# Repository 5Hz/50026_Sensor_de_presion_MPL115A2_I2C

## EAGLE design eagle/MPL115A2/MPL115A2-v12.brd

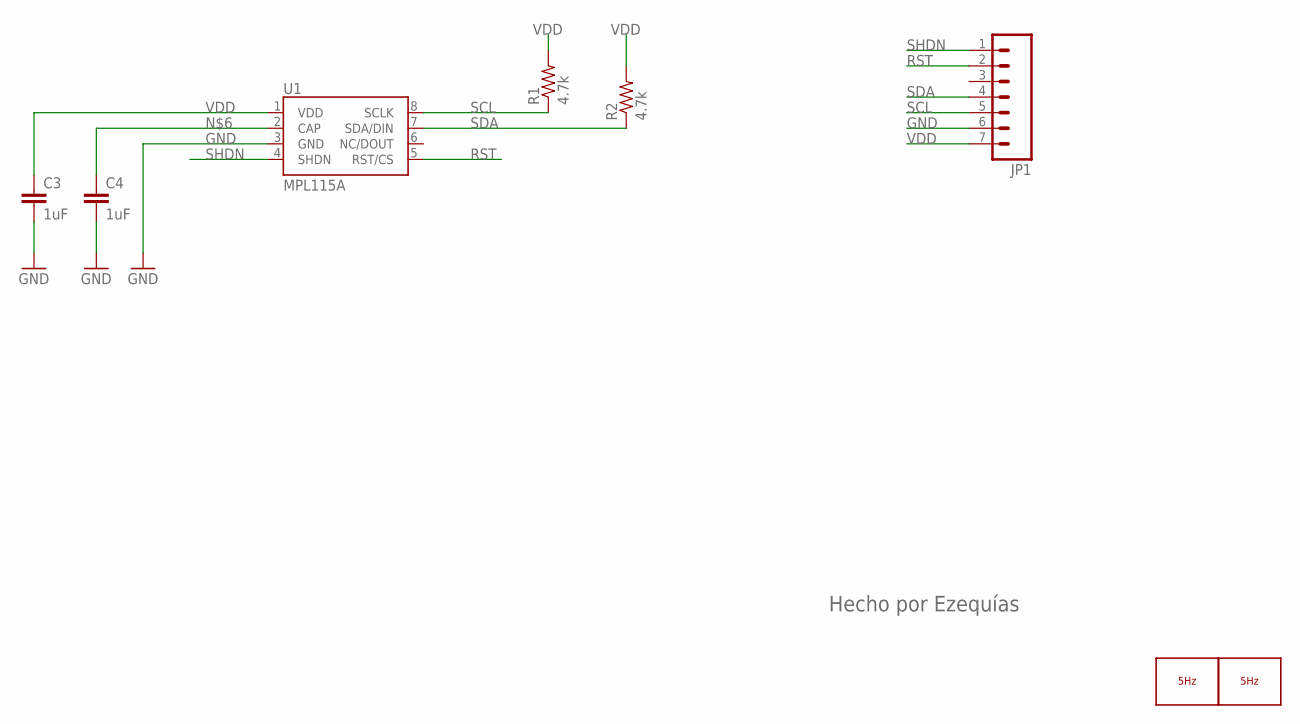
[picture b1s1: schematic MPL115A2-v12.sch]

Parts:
C3, C4: 1uF; 0805-CAP
JP1: M07; 1X07
LOGO1: LOGO_5HZ_H_5MM; 5HZ_LOGO_H_5MM
LOGO2: LOGO_5HZ_MINUSCULAS; 5HZ_LOGO_H_5MM
R1, R2: 4.7k; 1/6W-RES
U1: MPL115A; LGA8

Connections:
GND: C3.2, C4.2, JP1.6, U1.3 (GND)
unnamed: C4.1, U1.2 (CAP)
RST: JP1.2, U1.5 (RST/CS)
SCL: JP1.5, R1.1, U1.8 (SCLK)
SDA: JP1.4, R2.1, U1.7 (SDA/DIN)
SHDN: JP1.1, U1.4 (SHDN)
VDD: C3.1, JP1.7, R1.2, R2.2, U1.1 (VDD)

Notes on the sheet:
Hecho por Ezequías

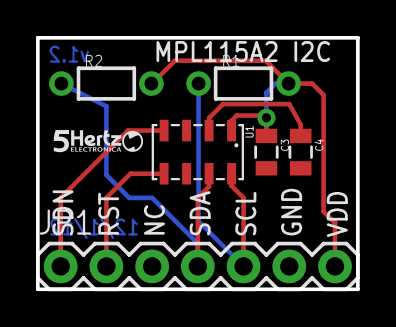
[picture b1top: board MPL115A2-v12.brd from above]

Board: 2 copper layers, 17.8 x 14.0 mm, 8 parts (1 on the bottom side), 7 nets.

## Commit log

2014-01-10 creación
